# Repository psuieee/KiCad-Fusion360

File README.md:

# KiCad-Fusion360

 Workshop 4 of Fall 2025.

## Requirements

This workshop requires the KiCad and Fusion 360 software. Download here.

KiCad: https://www.kicad.org/download/

Fusion 360: https://www.autodesk.com/education/edu-software/fusion

## Additional Items
- Completed KiCad files <br>
- Completed Fusion 360 files <br>
- Slideshow for the workshop

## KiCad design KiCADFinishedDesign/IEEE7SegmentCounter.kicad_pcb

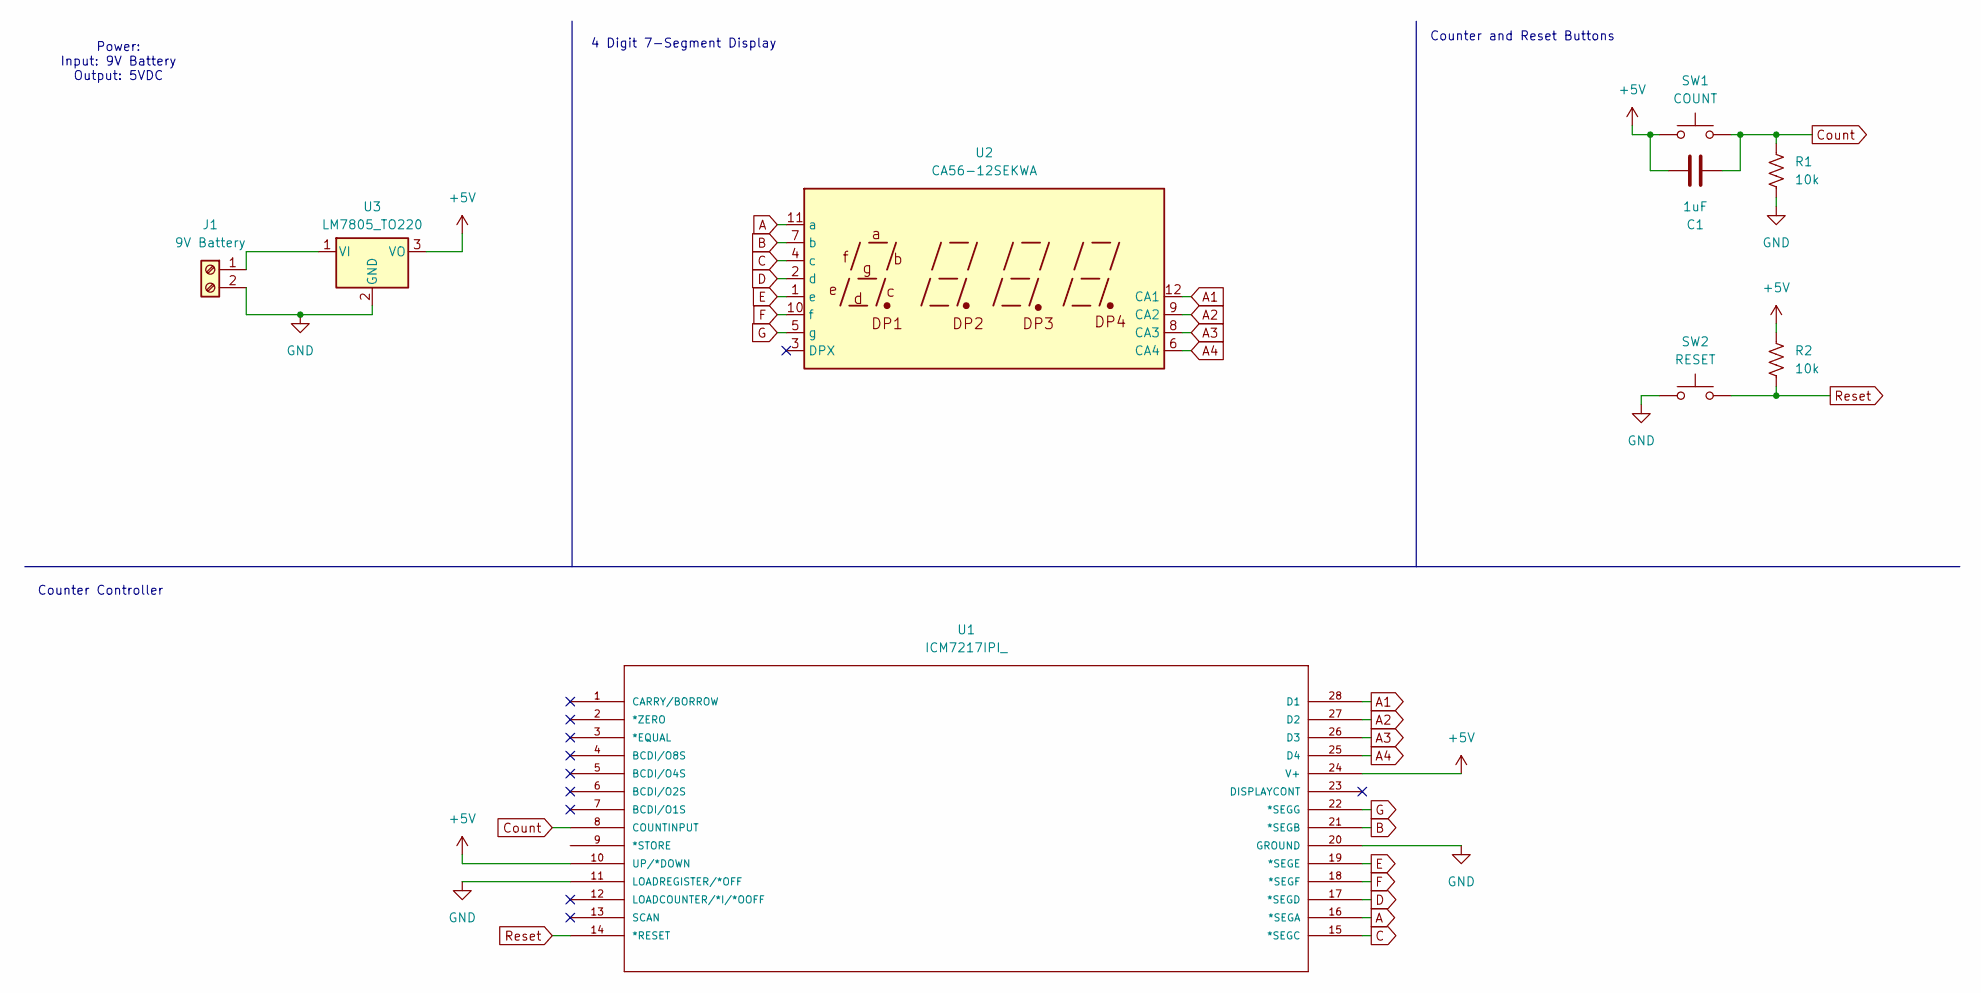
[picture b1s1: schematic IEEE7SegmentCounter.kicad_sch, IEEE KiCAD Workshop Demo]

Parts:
C1: 1uF; C_0603_1608Metric
J1: 9V Battery; TerminalBlock_Phoenix_PT-1,5-2-5.0-H_1x02_P5.00mm_Horizontal
R1, R2: 10k; R_0603_1608Metric
SW1: COUNT; SW_PUSH_6mm
SW2: RESET; SW_PUSH_6mm
U1: ICM7217IPI_; 21-0044B_28; MANUFACTURER_PART_NUMBER ICM7217IPI+
U2: CA56-12SEKWA
U3: LM7805_TO220; TO-220-3_Vertical

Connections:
+5V: C1.1, R2.2, SW1.1, U1.10 (UP/*DOWN), U1.24 (V+), U3.3 (VO)
A: U1.16 (*SEGA), U2.11 (a)
A1: U1.28 (D1), U2.12 (CA1)
A2: U1.27 (D2), U2.9 (CA2)
A3: U1.26 (D3), U2.8 (CA3)
A4: U1.25 (D4), U2.6 (CA4)
B: U1.21 (*SEGB), U2.7 (b)
C: U1.15 (*SEGC), U2.4 (c)
Count: C1.2, R1.1, SW1.2, U1.8 (COUNTINPUT)
D: U1.17 (*SEGD), U2.2 (d)
E: U1.19 (*SEGE), U2.1 (e)
F: U1.18 (*SEGF), U2.10 (f)
G: U1.22 (*SEGG), U2.5 (g)
GND: J1.2, R1.2, SW2.1, U1.11 (LOADREGISTER/*OFF), U1.20 (GROUND), U3.2 (GND)
unnamed: J1.1, U3.1 (VI)
Reset: R2.1, SW2.2, U1.14 (*RESET)

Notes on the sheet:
Counter Controller
Counter and Reset Buttons
Power: Input: 9V Battery Output: 5VDC
4 Digit 7-Segment Display

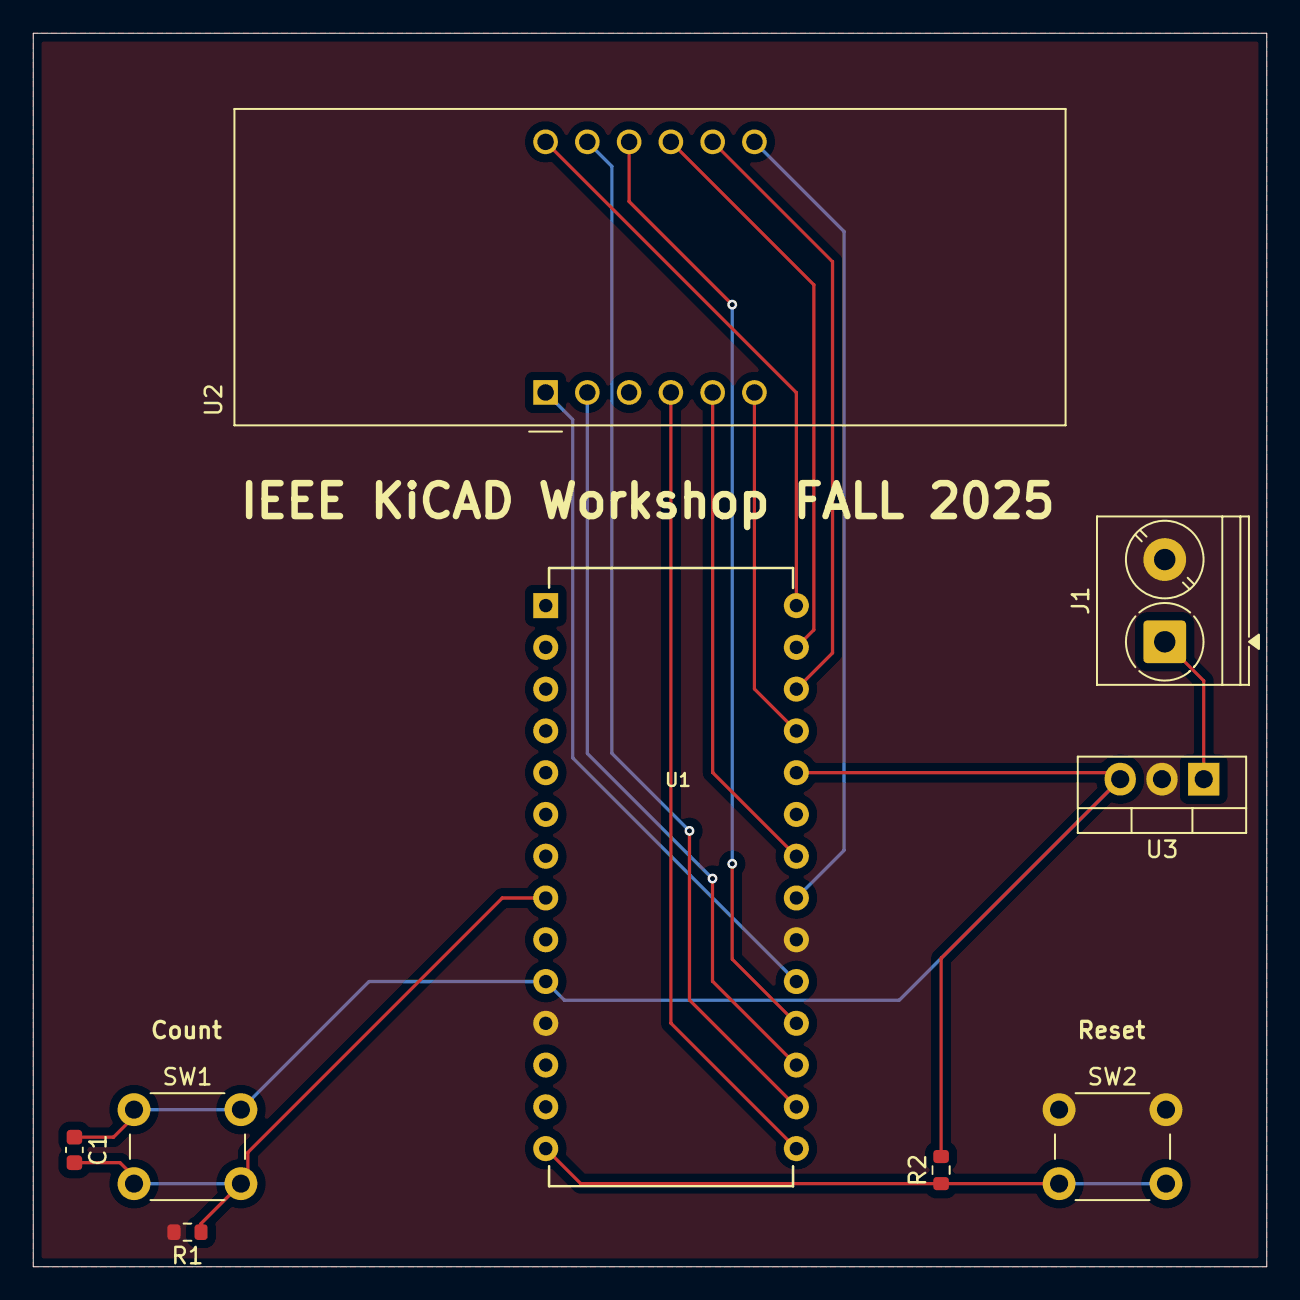
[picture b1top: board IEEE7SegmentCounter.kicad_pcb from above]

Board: 2 copper layers, 75.0 x 75.0 mm, 9 parts (0 on the bottom side), 16 nets.

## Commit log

2025-11-16 Added finished PCB files
2025-11-16 PPT Draft
